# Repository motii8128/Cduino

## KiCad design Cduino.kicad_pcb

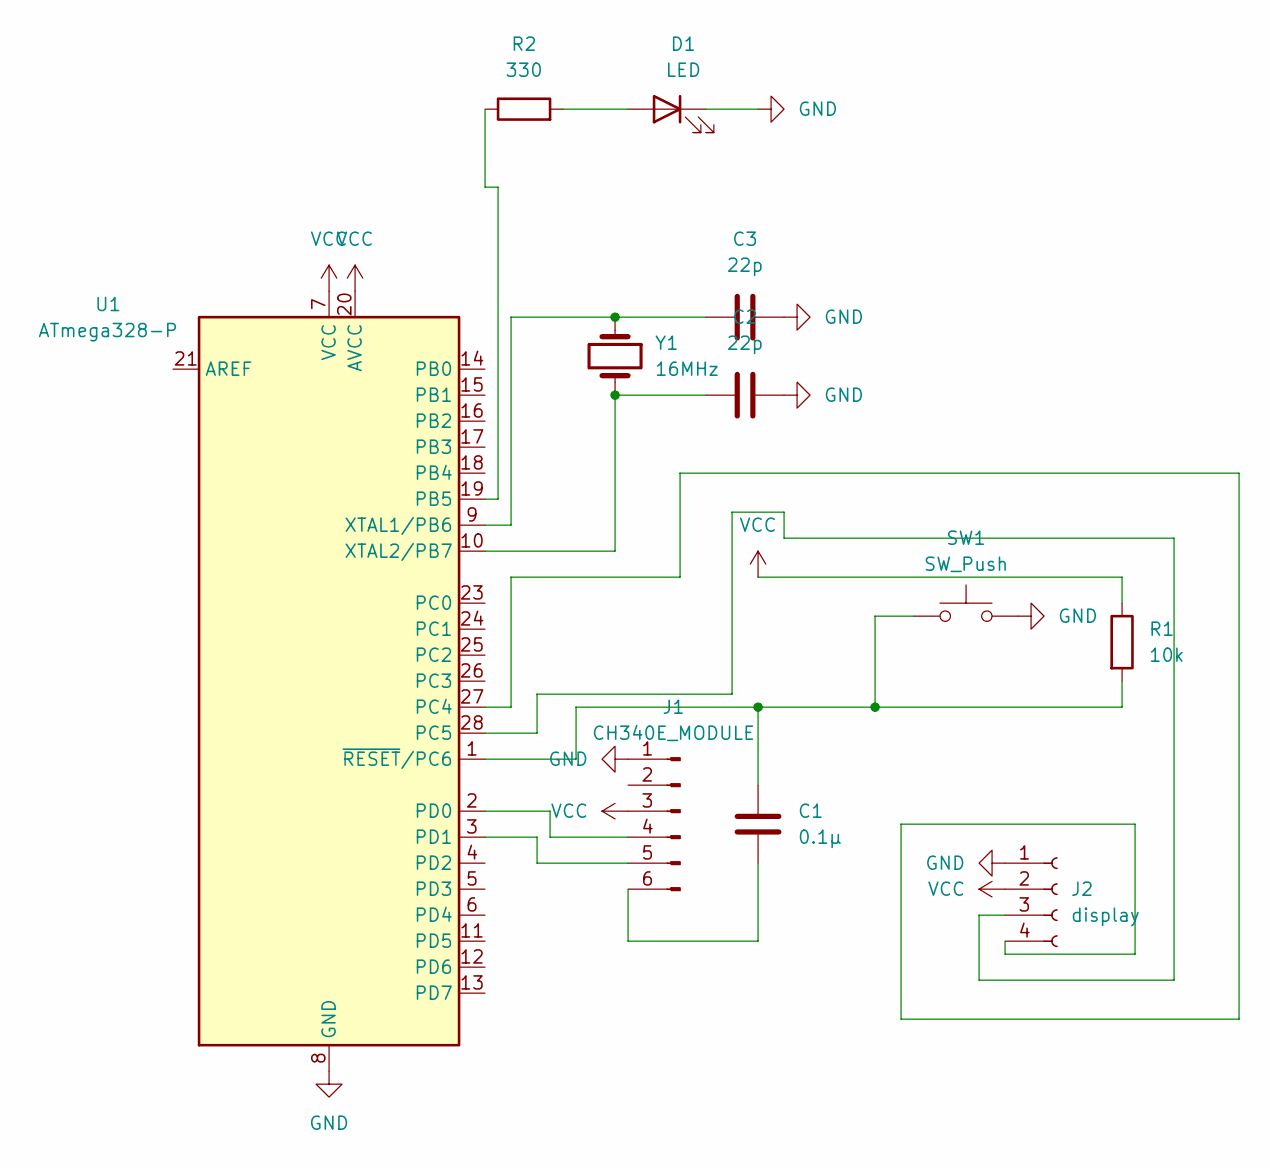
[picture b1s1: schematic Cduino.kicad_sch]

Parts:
C1: 0.1μ; C_Disc_D3.0mm_W2.0mm_P2.50mm
C2, C3: 22p; C_Disc_D3.0mm_W2.0mm_P2.50mm
D1: LED; LED_D5.0mm
J1: CH340E_MODULE; PinHeader_1x06_P2.54mm_Vertical
J2: display; PinSocket_1x04_P2.54mm_Vertical
R1: 10k; R_Axial_DIN0207_L6.3mm_D2.5mm_P10.16mm_Horizontal
R2: 330; R_Axial_DIN0207_L6.3mm_D2.5mm_P10.16mm_Horizontal
SW1: SW_Push; SW_PUSH_6mm
U1: ATmega328-P; DIP-28_W7.62mm
Y1: 16MHz; Crystal_HC18-U_Vertical

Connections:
GND: C2.2, C3.2, D1.1 (K), J1.1, J2.1, SW1.2, U1.8 (GND), U1.22 (GND)
unnamed: D1.2 (A), R2.2
unnamed: J1.4, U1.2 (PD0)
unnamed: J1.5, U1.3 (PD1)
unnamed: C1.2, J1.6
unnamed: J2.3, U1.28 (PC5)
unnamed: J2.4, U1.27 (PC4)
unnamed: R2.1, U1.19 (PB5)
unnamed: C3.1, U1.9 (XTAL1/PB6), Y1.1
unnamed: C2.1, U1.10 (XTAL2/PB7), Y1.2
unnamed: C1.1, R1.2, SW1.1, U1.1 (~RESET/PC6)
VCC: J1.3, J2.2, R1.1, U1.7 (VCC), U1.20 (AVCC)

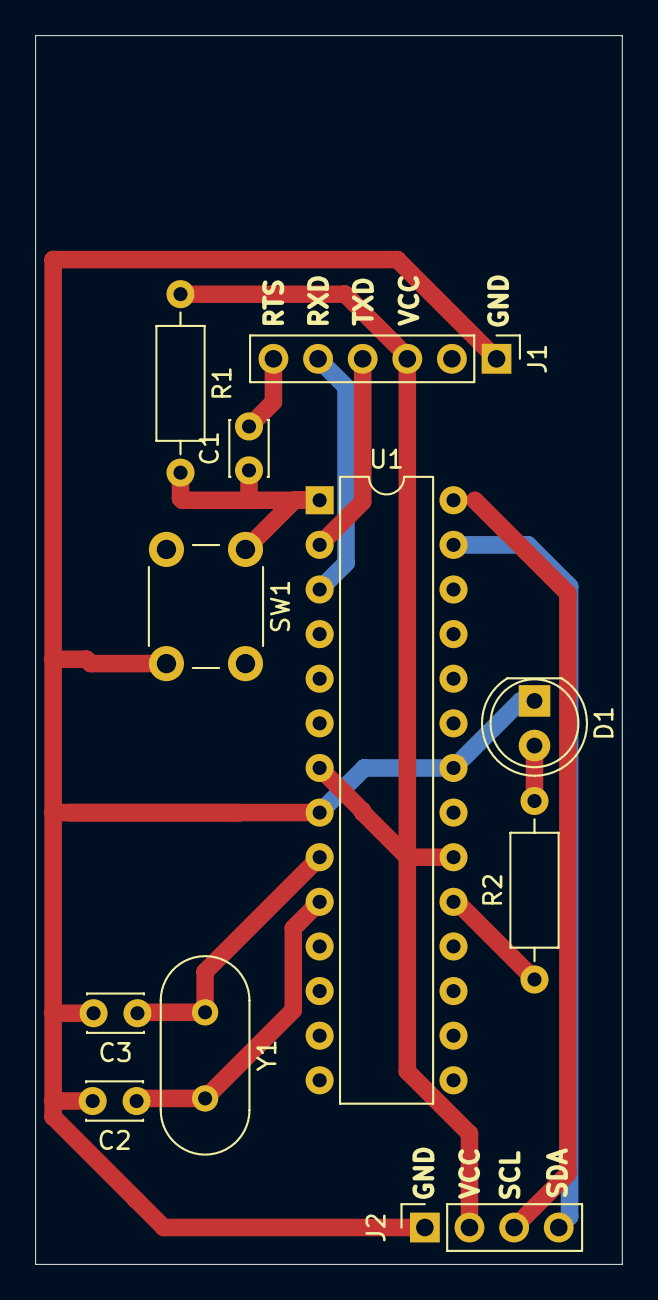
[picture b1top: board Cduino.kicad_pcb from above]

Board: 2 copper layers, 33.4 x 70.0 mm, 11 parts (0 on the bottom side), 12 nets.
